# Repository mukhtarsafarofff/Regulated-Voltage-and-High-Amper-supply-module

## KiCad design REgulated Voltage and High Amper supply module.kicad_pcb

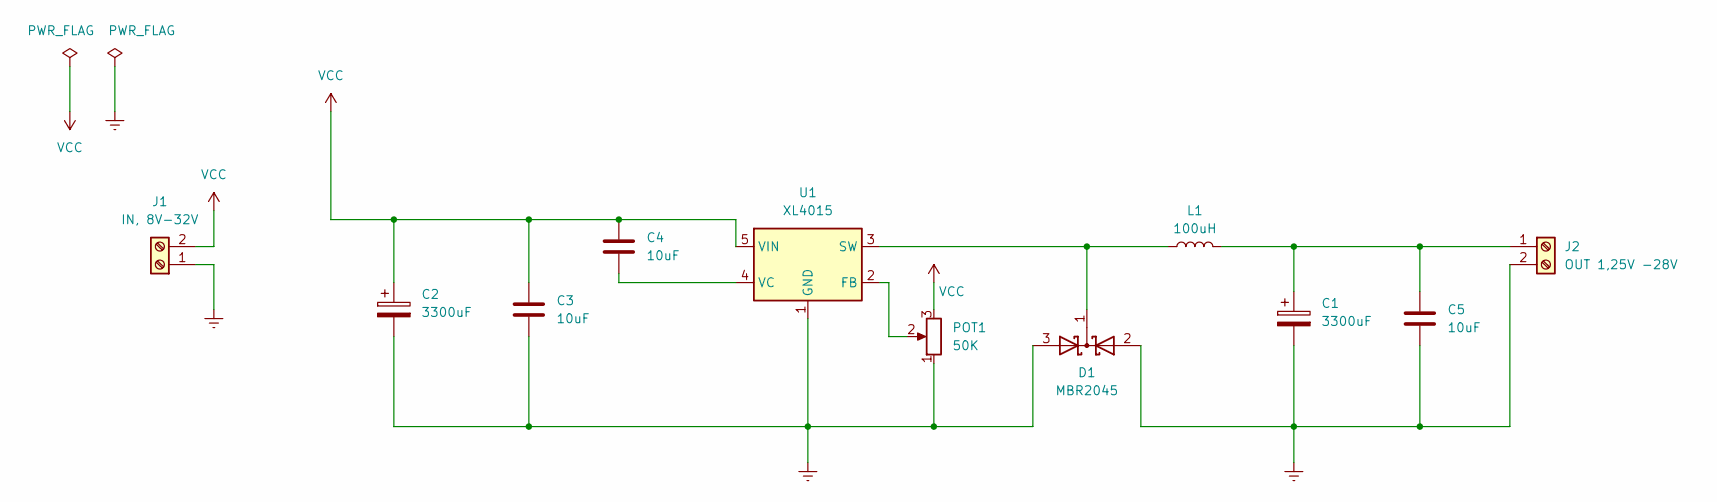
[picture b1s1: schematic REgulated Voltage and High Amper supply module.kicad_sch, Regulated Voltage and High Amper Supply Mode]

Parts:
C1, C2: 3300uF; CP_Radial_D10.0mm_P7.50mm
C3, C4, C5: 10uF; C_Disc_D10.5mm_W5.0mm_P7.50mm
D1: MBR2045; TO-220-3_Vertical
J1: IN, 8V-32V; TerminalBlock_bornier-2_P5.08mm
J2: OUT 1,25V -28V; TerminalBlock_bornier-2_P5.08mm
L1: 100uH; L_Toroid_Vertical_L17.8mm_W9.7mm_P7.11mm_Pulse_B
POT1: 50K; Potentiometer_Vishay_148-149_Single_Horizontal
U1: XL4015; TO-263-5_TabPin3

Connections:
Earth: C1.2, C2.2, C3.1, C5.1, D1.2 (A), D1.3 (A), J1.1, J2.2, POT1.1, U1.1 (GND)
unnamed: D1.1 (K), L1.1, U1.3 (SW)
unnamed: C1.1, C5.2, J2.1, L1.2
unnamed: POT1.2, U1.2 (FB)
unnamed: C4.1, U1.4 (VC)
VCC: C2.1, C3.2, C4.2, J1.2, POT1.3, U1.5 (VIN)

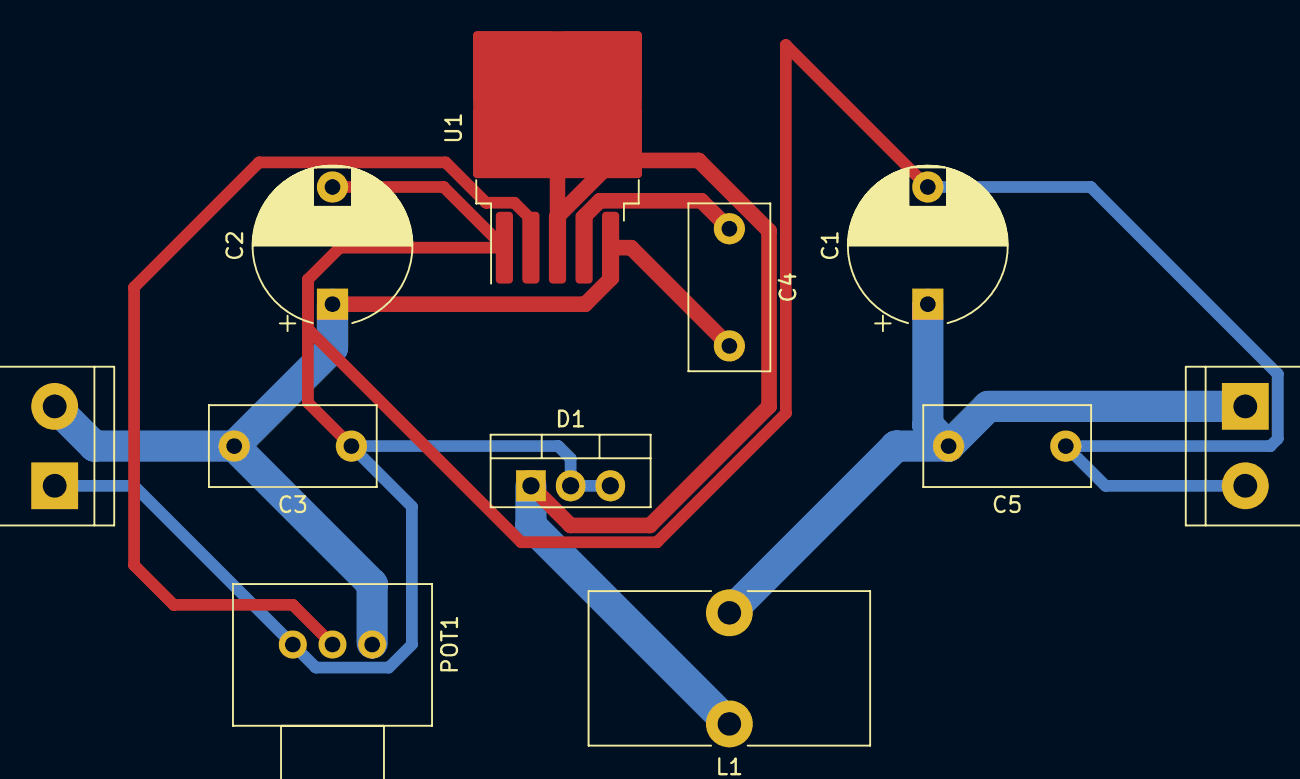
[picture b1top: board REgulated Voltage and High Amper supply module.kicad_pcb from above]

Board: 2 copper layers, 11 parts (0 on the bottom side), 6 nets.

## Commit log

2024-03-17 Regulated Voltage and igh Amper supply module is accomplished
2024-03-17 Unneeded folder is deleted
2024-03-26 Regulated Voltage and High Amper supply Module is renewed
